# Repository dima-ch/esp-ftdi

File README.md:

# esp-ftdi
Adapter for remote programming an arduino via WiFi with the ESP8266

ESP8266 firmware https://github.com/beckdac/ESP8266-transparent-bridge

Flash script:
```
#!/bin/bash

HEXILE="firmware.hex"
ADDRESS=x.x.x.x
BAUD=57600

echo "+++AT BAUD $BAUD" | nc $(ADDRESS) 23
echo "+++AT GPIO2 1" | nc $(ADDRESS) 23
echo "+++AT GPIO2 0" | nc $(ADDRESS) 23
avrdude -P net:$(ADDRESS):23 -F -U flash:w:$(HEXILE):i
```

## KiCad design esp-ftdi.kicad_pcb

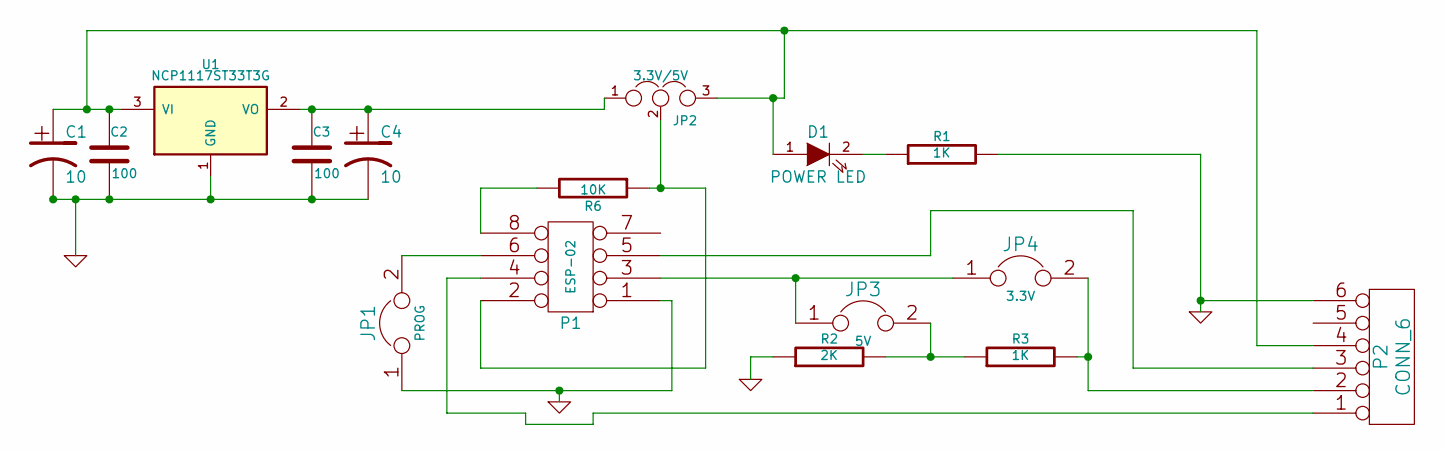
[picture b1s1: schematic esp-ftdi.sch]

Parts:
C1, C4: 10
C2, C3: 100
D1: POWER LED
JP1: PROG
JP2: 3.3V/5V
JP3: 5V
JP4: 3.3V
P1: ESP-02
P2: CONN_6
R1, R3: 1K
R2: 2K
R6: 10K
U1: NCP1117ST33T3G

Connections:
GND: C1.2, C2.2, C3.2, C4.2, JP1.1, P1.1, P2.6, R1.2, R2.1, U1.1 (GND)
unnamed: D1.2 (K), R1.1
unnamed: JP3.2, R2.2, R3.1
unnamed: JP4.2, P2.2, R3.2
unnamed: JP3.1, JP4.1, P1.3
unnamed: P1.5, P2.3
unnamed: C1.1, C2.1, D1.1 (A), JP2.3, P2.4, U1.3 (VI)
unnamed: C3.1, C4.1, JP2.1, U1.2 (VO)
unnamed: JP1.2, P1.6
unnamed: P1.4, P2.1
unnamed: P1.8, R6.2
unnamed: JP2.2, P1.2, R6.1

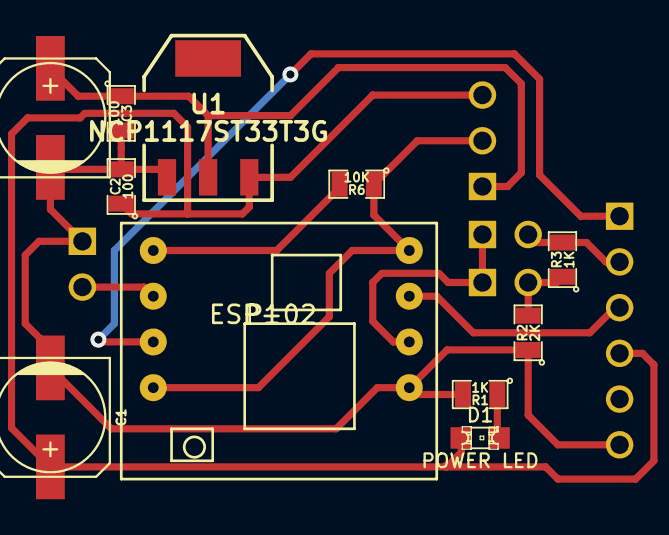
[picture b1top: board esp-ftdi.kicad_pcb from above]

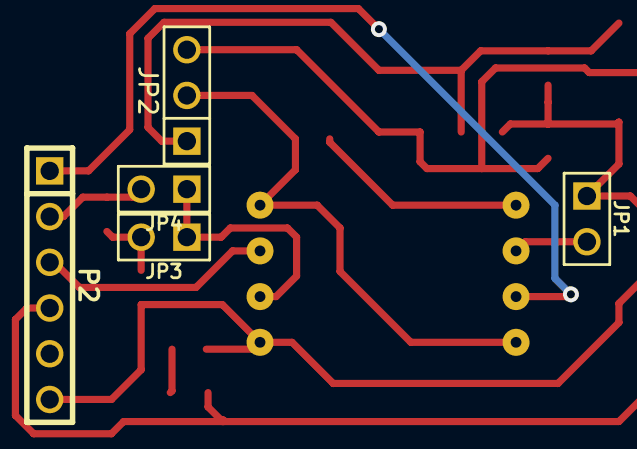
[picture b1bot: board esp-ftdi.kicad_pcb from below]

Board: 2 copper layers, 16 parts (5 on the bottom side), 12 nets.

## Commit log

2016-04-10 init
